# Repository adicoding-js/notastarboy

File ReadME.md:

# notastarboy

notastarboy is a motion-controlled desktop pet that remembers you. It's project that i made by following the Starbie Week 1 guide, it has same hardware, same tilt-to-select menu, but instead of just saving three stat numbers, it keeps a log of your last 16 interactions + lifetime totals, all stored in the flash meomory so they survive a reboot. A new MOOD view reads that log and calls the pet out if you've been ignoring it.

## What it is

notastarboy sits on your desk, shows its personality on a small OLED, and reacts to how you handle it. Tilting opens a radial menu (NAP / PLAY / FEED / PET), shaking does a quick stat bump on its own. Everything still runs on a microcontroller, display, motion sensor, and environmental sensor in a compact through-hole PCB.

What's different from stock Starbie: every action gets logged, not just applied and forgotten. Press button 2 twice to pull up the MOOD view and see FED / PLAYED / NAPPED / PET / SHAKEN totals, how many entries are currently logged, and a one-word callout (HUNGRY / BORED / LONELY) if you've left one stat untouched for 6+ hours.

### Bill of materials(BOM)

| Item | Description | Qty | Unit Price (AUD) | Line Total (AUD) | Link |
|------|-------------|-----|------------------|------------------|------|
| 1 | Beetle ESP32-C3 (RISC-V Core Development Board), main microcontroller for all the processing | 1 | $8.50 | $8.50 | [Link](https://robocraze.com/products/beetle-esp32-c3-risc-v-core-development-board?_pos=1&_psq=esp32+c3&_psid=18ba7251c&_ss=e) |
| 2 | MPU6050, gyroscope and motion detection | 1 | $1.70 | $1.70 | [Link](https://robocraze.com/products/mpu-6050-triple-axis-accelerometer-gyroscope-module?_pos=1&_psq=MPU6050&_psid=26e4c4fb9&_ss=e) |
| 3 | DHT11, environment sensing | 1 | $0.70 | $0.70 | [Link](https://robocraze.com/products/dht11-humidity-and-temperature-sensor?_pos=2&_sid=9e06e5b0b&_ss=r) |
| 4 | 0.96" OLED Display, display for showing main pet | 1 | $1.80 | $1.80 | [Link](https://robocraze.com/products/0-96in-oled-display-module-4pin?_pos=1&_psq=0.96+OLED&_psid=bfed60e23&_ss=e) |
| 5 | Resistors, resistors for resisting current | 1 | $0.50 | $0.50 | [Link](https://robocraze.com/products/resistor-box?_pos=1&_sid=7e886e4f5&_ss=r) |
| 6 | MX Switches, for interaction | 1 | $5.17 | $5.17 | [Link](https://www.amazon.in/Buildcon-Mechanical-Keyboard-Universal-Keyboards/dp/B0GCCQLQBV/) |
| 7 | Keycaps, keycaps for switches | 1 | $11.00 | $11.00 | [Link](https://www.amazon.in/ZORBES-130-Key-Topographic-Mechanical-Keyboard/dp/B0GZMBPHYB/) |
| 8 | Tax and shipping for the whole order | – | – | $0.63 | – |
| | **Total** | | | **$30.00** | |

## Why?

This started as the week 1 beginner tutorial for halflife. The journal is the required departure from the guide, Starbie's own maintainers ask that submissions change more than the shape, so this adds actual firmware behavior on top instead of reskinning the same build.

## Software

`notastarboy.ino` is the self contained sketch i found in the guide and i added some changed to it so that mood+storage/interactions gets added as well, its not much but its not less as well.

## Known issues

A few cosmetic DRC warnings remain (silkscreen clipped by solder mask/board edge on the back graphic, J1's courtyard excluded since it's an imported footprint). None affect routing, copper, or manufacturability, see DRC reports in this repo for the full list.

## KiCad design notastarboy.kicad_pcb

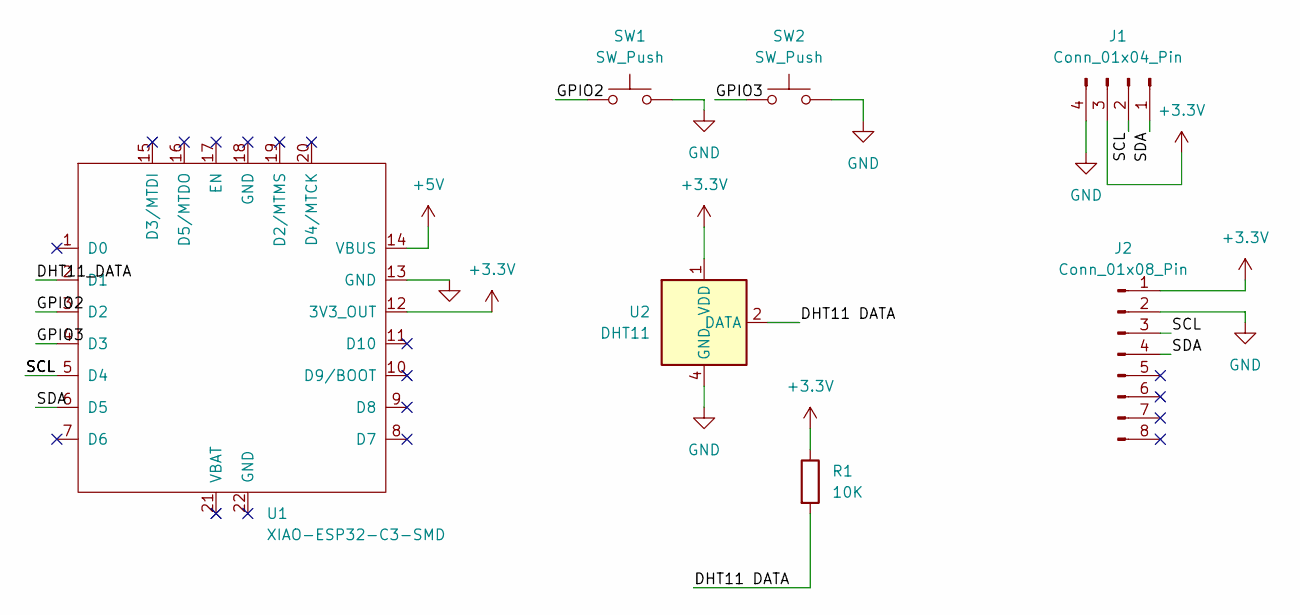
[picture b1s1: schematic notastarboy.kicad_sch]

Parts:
J1: Conn_01x04_Pin; Display_128x64_096_I2C
J2: Conn_01x08_Pin; MPU6050_Module
R1: 10K; R_Axial_DIN0204_L3.6mm_D1.6mm_P1.90mm_Vertical
SW1, SW2: SW_Push; SW_Cherry_MX_1.00u_PCB
U1: XIAO-ESP32-C3-SMD; XIAO-ESP32-C6-DIP
U2: DHT11; Aosong_DHT11_5.5x12.0_P2.54mm

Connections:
+3.3V: J1.3, J2.1, R1.1, U1.12 (3V3_OUT), U2.1 (VDD)
+5V: U1.14 (VBUS)
/DHT11 DATA: R1.2, U2.2 (DATA)
/DHT11_DATA: U1.2 (D1)
/GPIO2: SW1.1, U1.3 (D2)
/GPIO3: SW2.1, U1.4 (D3)
/SCL: J1.2, J2.3, U1.5 (D4)
/SDA: J1.1, J2.4, U1.6 (D5)
GND: J1.4, J2.2, SW1.2, SW2.2, U1.13 (GND), U2.4 (GND)

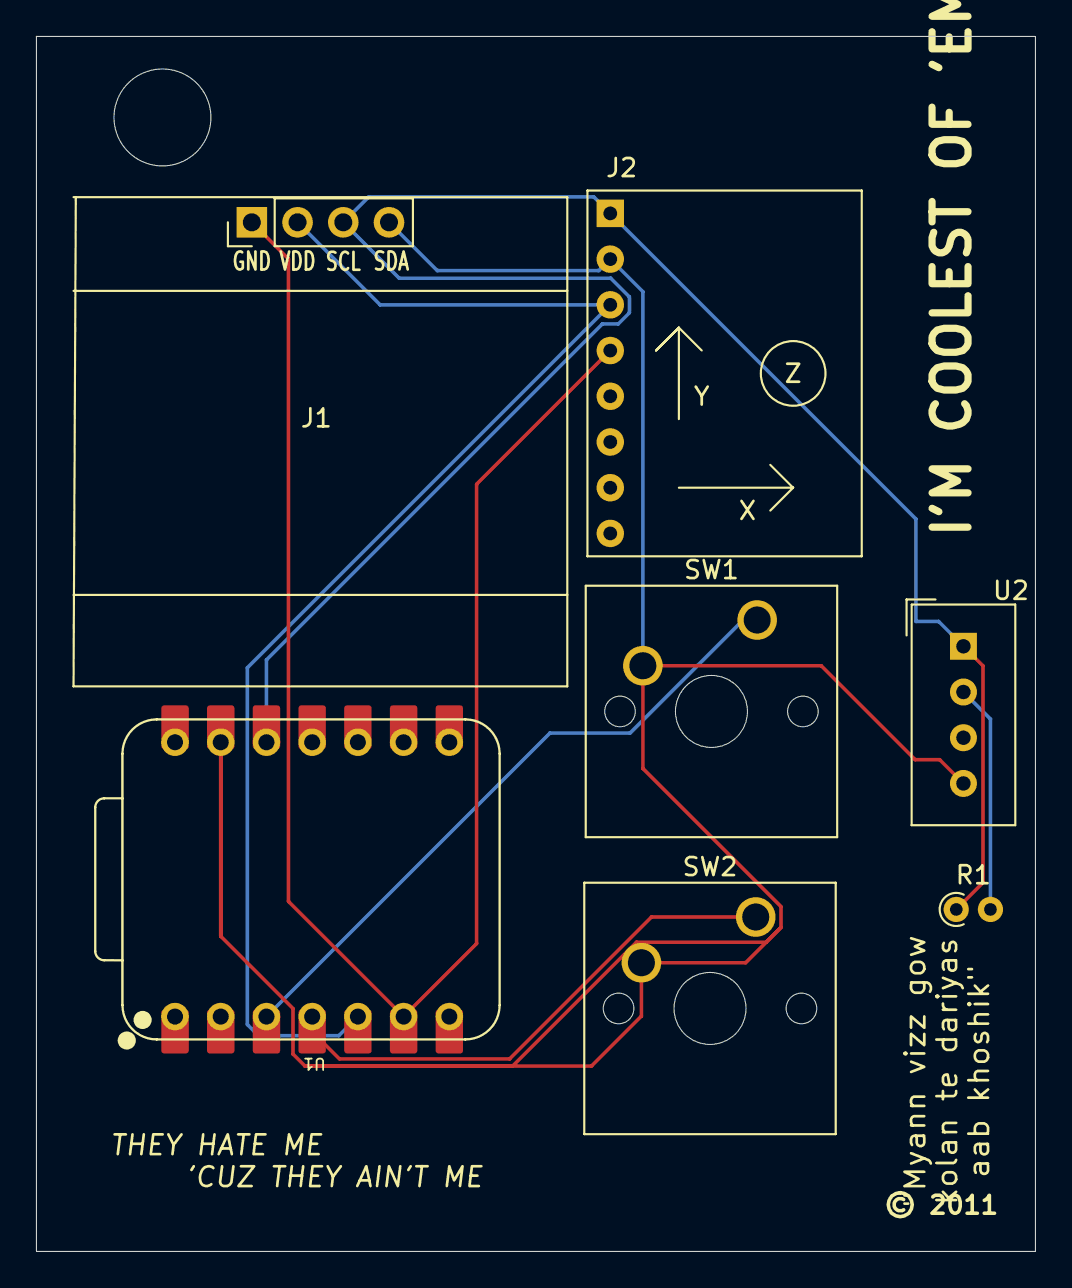
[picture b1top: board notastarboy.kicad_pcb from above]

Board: 2 copper layers, 55.5 x 67.5 mm, 7 parts (0 on the bottom side), 7 nets.

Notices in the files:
notastarboy.kicad_pcb:
© 2011
